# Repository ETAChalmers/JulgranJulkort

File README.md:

# X-mas tree card
# NOT TESTED (2022-12-21)
This PCB is a supposed to become a Christmas card from E-sectionens Teletekniska Avdelning (ETA). It is a 2,4 GHz antenna in the shape of a Christmas tree. According to the Wifi strength the card is exposed to, different LED's should light up, so it is basically a fancy bar graph.

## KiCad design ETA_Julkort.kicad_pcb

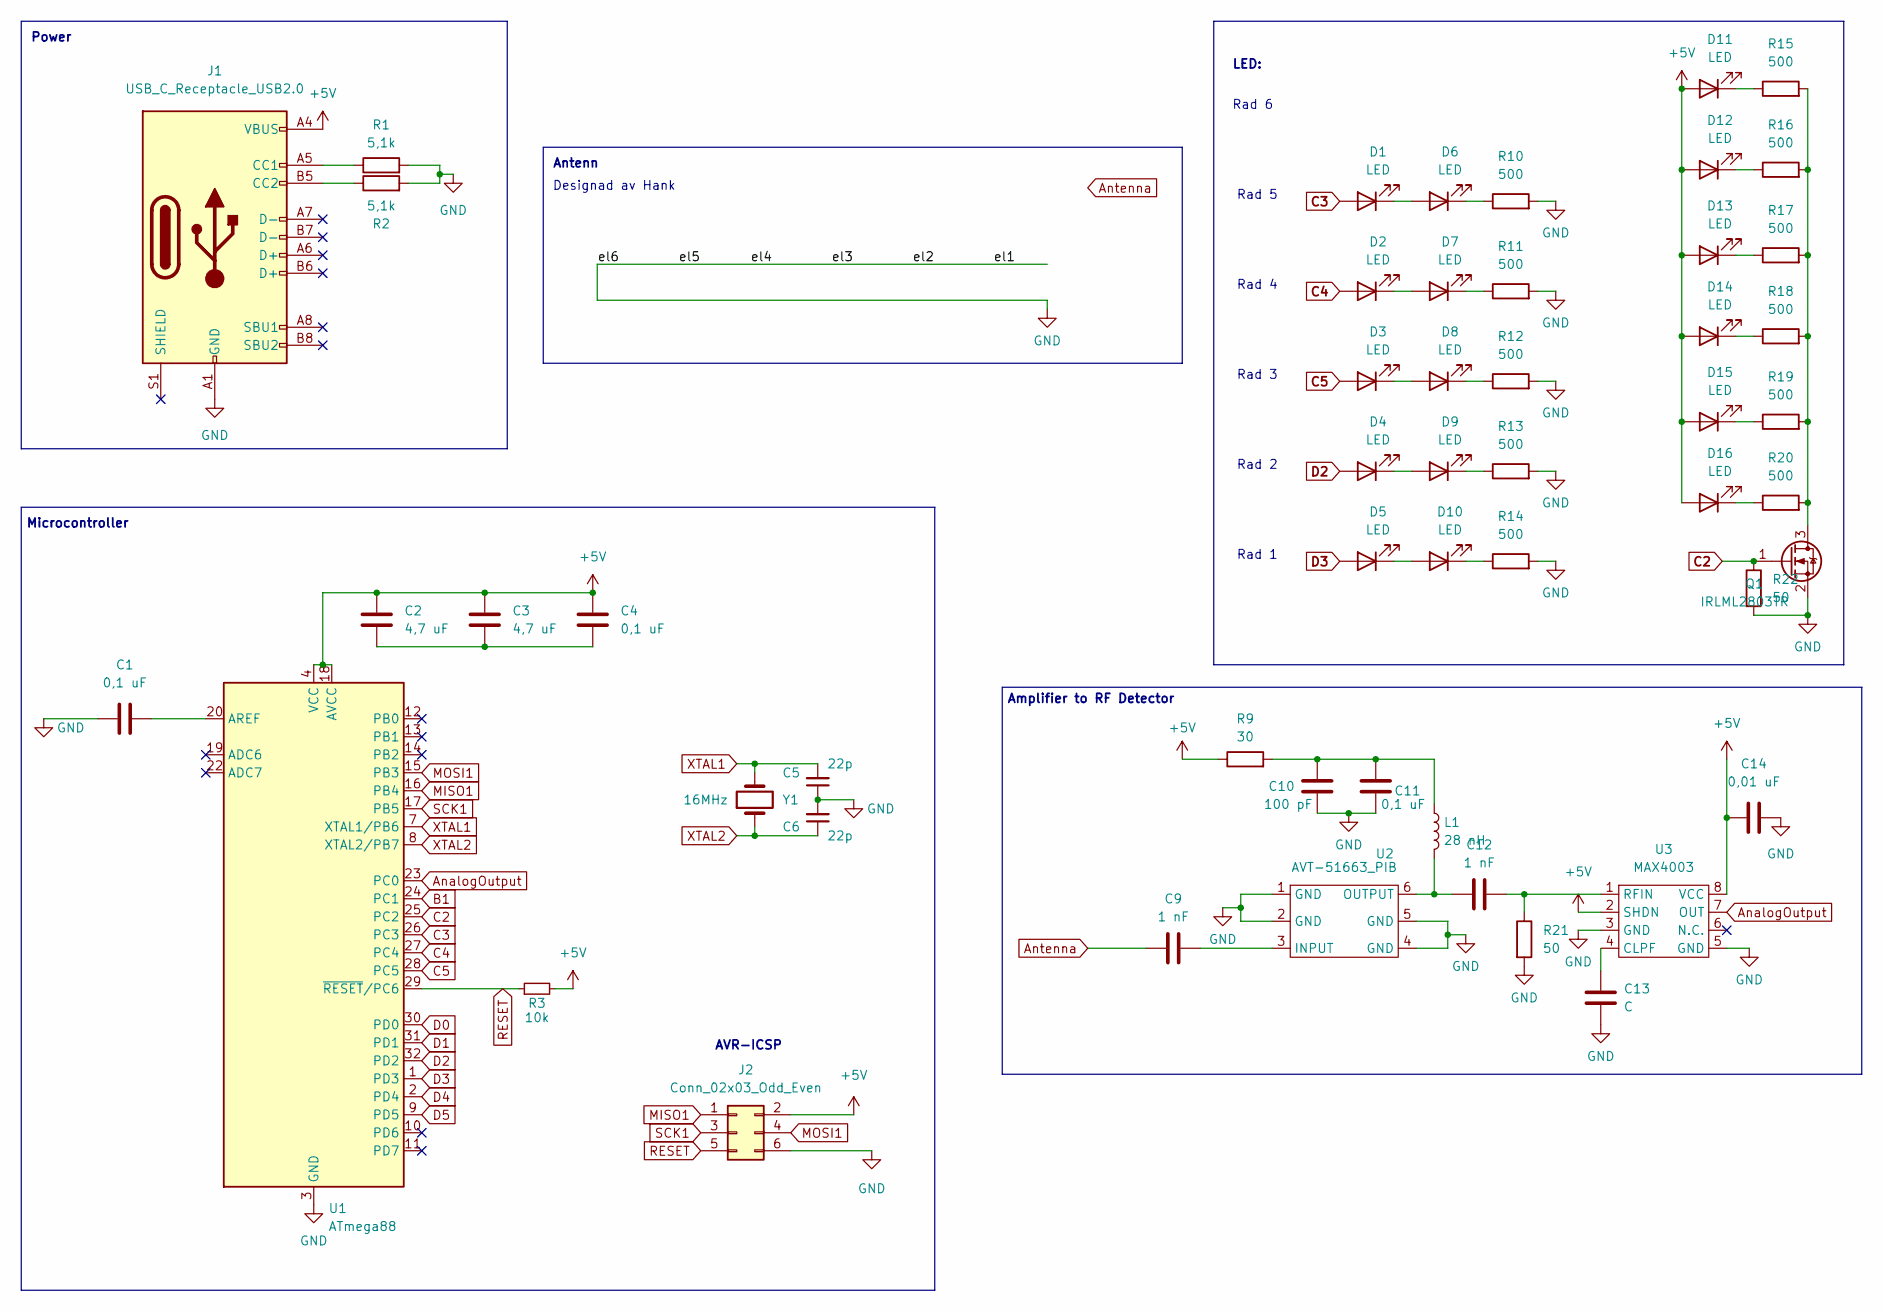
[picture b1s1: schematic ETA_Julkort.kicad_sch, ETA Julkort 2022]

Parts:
C1, C4, C11: 0,1 uF; C_0603_1608Metric
C2, C3: 4,7 uF; C_0805_2012Metric
C5, C6: 22p; C_0603_1608Metric
C9, C12: 1 nF; C_0603_1608Metric
C10: 100 pF; C_0603_1608Metric
C13: C; C_0603_1608Metric
C14: 0,01 uF; C_0603_1608Metric
D1, D2, D3, D4, D5, D6, D7, D8, D9, D10, D11, D12, D13, D14, D15, D16: LED; LED_0805_2012Metric
J1: USB_C_Receptacle_USB2.0; USB_C_Receptacle_JAE_DX07S016JA1R1500
J2: Conn_02x03_Odd_Even; PinSocket_2x03_P2.54mm_Vertical
L1: 28 nH; L_0603_1608Metric_Pad1.05x0.95mm_HandSolder
Q1: IRLML2803TR; SOT-23
R1, R2: 5,1k; R_0603_1608Metric
R3: 10k; R_0603_1608Metric
R9: 30; R_0603_1608Metric
R10, R11, R12, R13, R14, R15, R16, R17, R18, R19, R20: 500; R_0603_1608Metric
R21, R22: 50; R_0603_1608Metric
U1: ATmega88; TQFP-32_7x7mm_P0.8mm
U2: AVT-51663_PIB; SOT-363_SC-70-6
U3: MAX4003; MSOP-8_3x3mm_P0.65mm
Y1: 16MHz; Crystal_SMD_HC49-SD

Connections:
+5V: C2.1, C3.1, C4.1, C14.1, D11.2 (A), D12.2 (A), D13.2 (A), D14.2 (A), D15.2 (A), D16.2 (A), J1.A4 (VBUS), J1.A9 (VBUS), J1.B4 (VBUS), J1.B9 (VBUS), J2.2, R3.2, R9.1, U1.4 (VCC), U1.6 (VCC), U1.18 (AVCC), U3.2 (SHDN), U3.8 (VCC)
AnalogOutput: U1.23 (PC0), U3.7 (OUT)
B1: U1.24 (PC1)
C2: Q1.1 (G), R22.1, U1.25 (PC2)
C3: D1.2 (A), U1.26 (PC3)
C4: D2.2 (A), U1.27 (PC4)
C5: D3.2 (A), U1.28 (PC5)
D0: U1.30 (PD0)
D1: U1.31 (PD1)
D2: D4.2 (A), U1.32 (PD2)
D3: D5.2 (A), U1.1 (PD3)
D4: U1.2 (PD4)
D5: U1.9 (PD5)
MISO1: J2.1, U1.16 (PB4)
MOSI1: J2.4, U1.15 (PB3)
unnamed: C1.2, U1.20 (AREF)
unnamed: C2.2, C3.2, C4.2
unnamed: C9.2, U2.3 (INPUT)
unnamed: C10.1, C11.1, L1.1, R9.2
unnamed: C12.1, L1.2, U2.6 (OUTPUT)
unnamed: C12.2, R21.1, U3.1 (RFIN)
unnamed: C13.1, U3.4 (CLPF)
unnamed: D1.1 (K), D6.2 (A)
unnamed: D2.1 (K), D7.2 (A)
unnamed: D3.1 (K), D8.2 (A)
unnamed: D4.1 (K), D9.2 (A)
unnamed: D6.1 (K), R10.1
unnamed: D7.1 (K), R11.1
unnamed: D8.1 (K), R12.1
unnamed: D9.1 (K), R13.1
unnamed: D10.1 (K), R14.1
unnamed: D5.1 (K), D10.2 (A)
unnamed: D11.1 (K), R15.1
unnamed: D12.1 (K), R16.1
unnamed: D13.1 (K), R17.1
unnamed: D14.1 (K), R18.1
unnamed: D15.1 (K), R19.1
unnamed: D16.1 (K), R20.1
unnamed: J1.A5 (CC1), R1.1
unnamed: J1.B5 (CC2), R2.1
unnamed: Q1.3 (D), R15.2, R16.2, R17.2, R18.2, R19.2, R20.2
RESET: J2.5, R3.1, U1.29 (~RESET/PC6)
SCK1: J2.3, U1.17 (PB5)
XTAL1: C5.2, U1.7 (XTAL1/PB6), Y1.2
XTAL2: C6.1, U1.8 (XTAL2/PB7), Y1.1

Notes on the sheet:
Microcontroller
Rad 5
Rad 6
Designad av Hank
Amplifier to RF Detector
LED:
Rad 2
Antenn
Rad 4
Rad 1
Rad 3
AVR-ICSP
Power

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
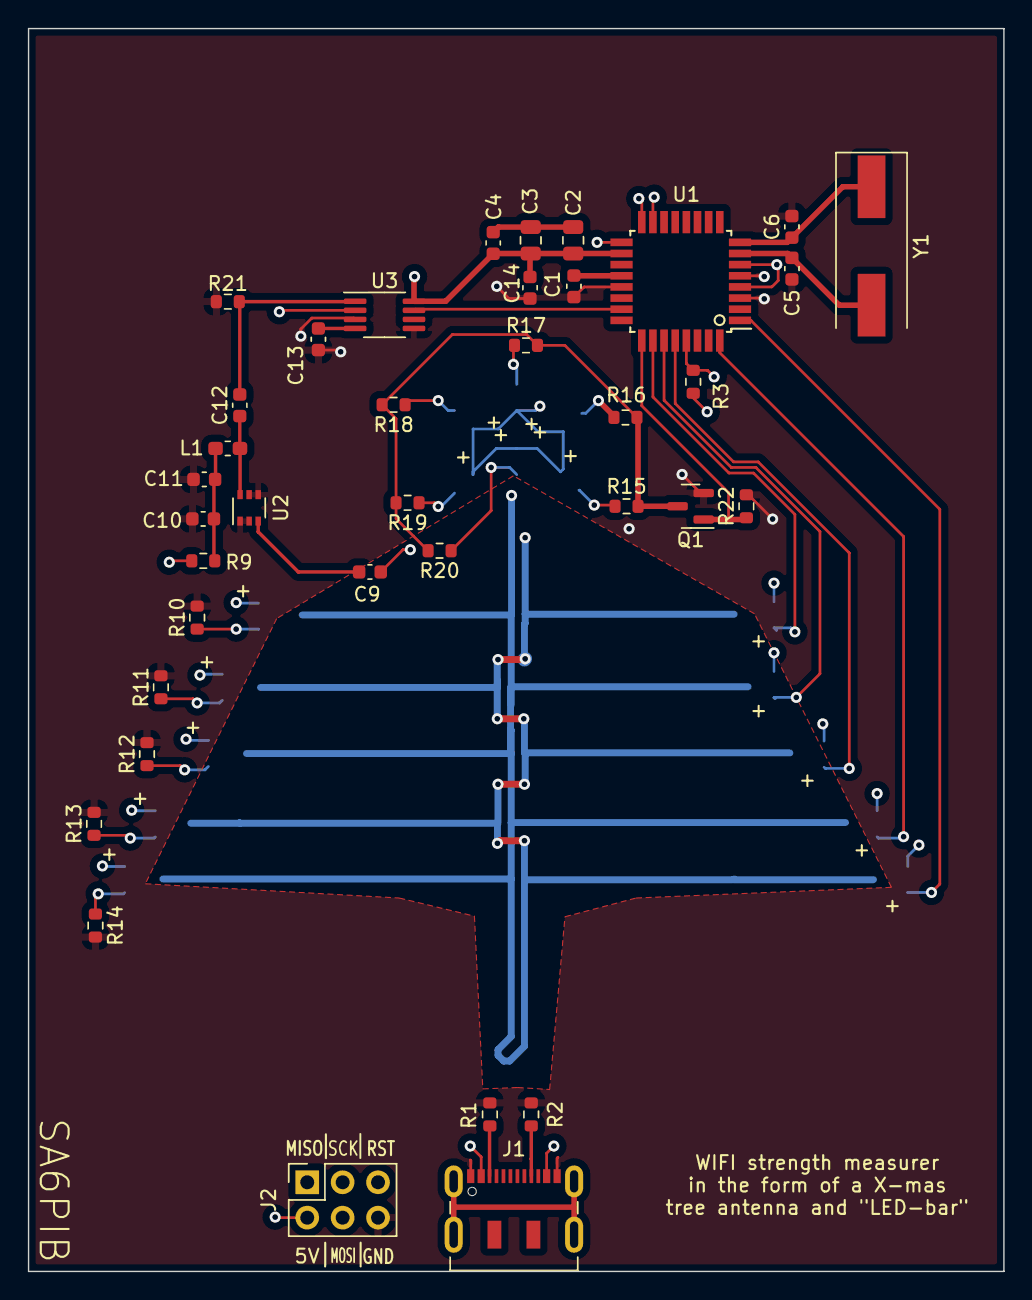
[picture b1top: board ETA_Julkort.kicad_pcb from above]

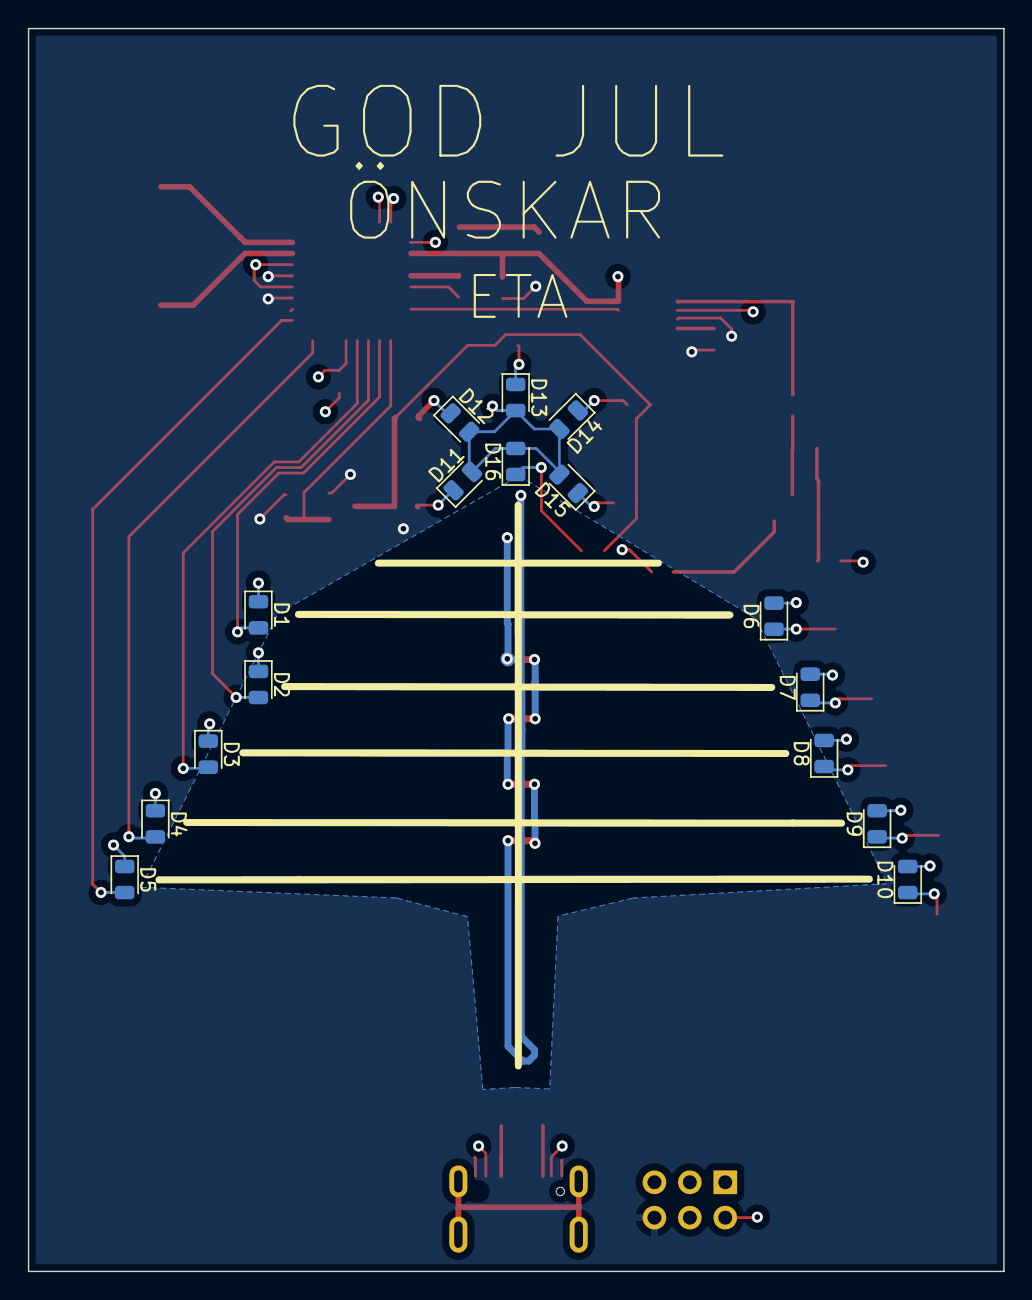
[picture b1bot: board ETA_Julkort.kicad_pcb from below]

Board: 4 copper layers, 70.0 x 89.2 mm, 53 parts (16 on the bottom side), 41 nets.

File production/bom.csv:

Designator,Footprint,Quantity,Value,LCSC Part #
"C1, C11, C4",C_0603_1608Metric,3,"0,1 uF",
C10,C_0603_1608Metric,1,100 pF,
"C12, C9",C_0603_1608Metric,2,1 nF,
C13,C_0603_1608Metric,1,C,
C14,C_0603_1608Metric,1,"0,01 uF",
"C2, C3",C_0805_2012Metric,2,"4,7 uF",
"C5, C6",C_0603_1608Metric,2,22p,
"D1, D10, D11, D12, D13, D14, D15, D16, D2, D3, D4, D5, D6, D7, D8, D9",LED_0805_2012Metric,16,LED,
J1,USB_C_Receptacle_JAE_DX07S016JA1R1500,1,USB_C_Receptacle_USB2.0,
J2,PinSocket_2x03_P2.54mm_Vertical,1,Conn_02x03_Odd_Even,
L1,L_0603_1608Metric_Pad1.05x0.95mm_HandSolder,1,28 nH,
Q1,SOT-23,1,IRLML2803TR,
"R1, R2",R_0603_1608Metric,2,"5,1k",
"R10, R11, R12, R13, R14, R15, R16, R17, R18, R19, R20",R_0603_1608Metric,11,500,
"R21, R22",R_0603_1608Metric,2,50,
R3,R_0603_1608Metric,1,10k,
R9,R_0603_1608Metric,1,30,
U1,TQFP-32_7x7mm_P0.8mm,1,ATmega88,
U2,SOT-363_SC-70-6,1,AVT-51663_PIB,
U3,MSOP-8_3x3mm_P0.65mm,1,MAX4003,
Y1,Crystal_SMD_HC49-SD,1,16MHz,

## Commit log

2022-12-14 Added Kicad
2022-12-14 Added pictures
